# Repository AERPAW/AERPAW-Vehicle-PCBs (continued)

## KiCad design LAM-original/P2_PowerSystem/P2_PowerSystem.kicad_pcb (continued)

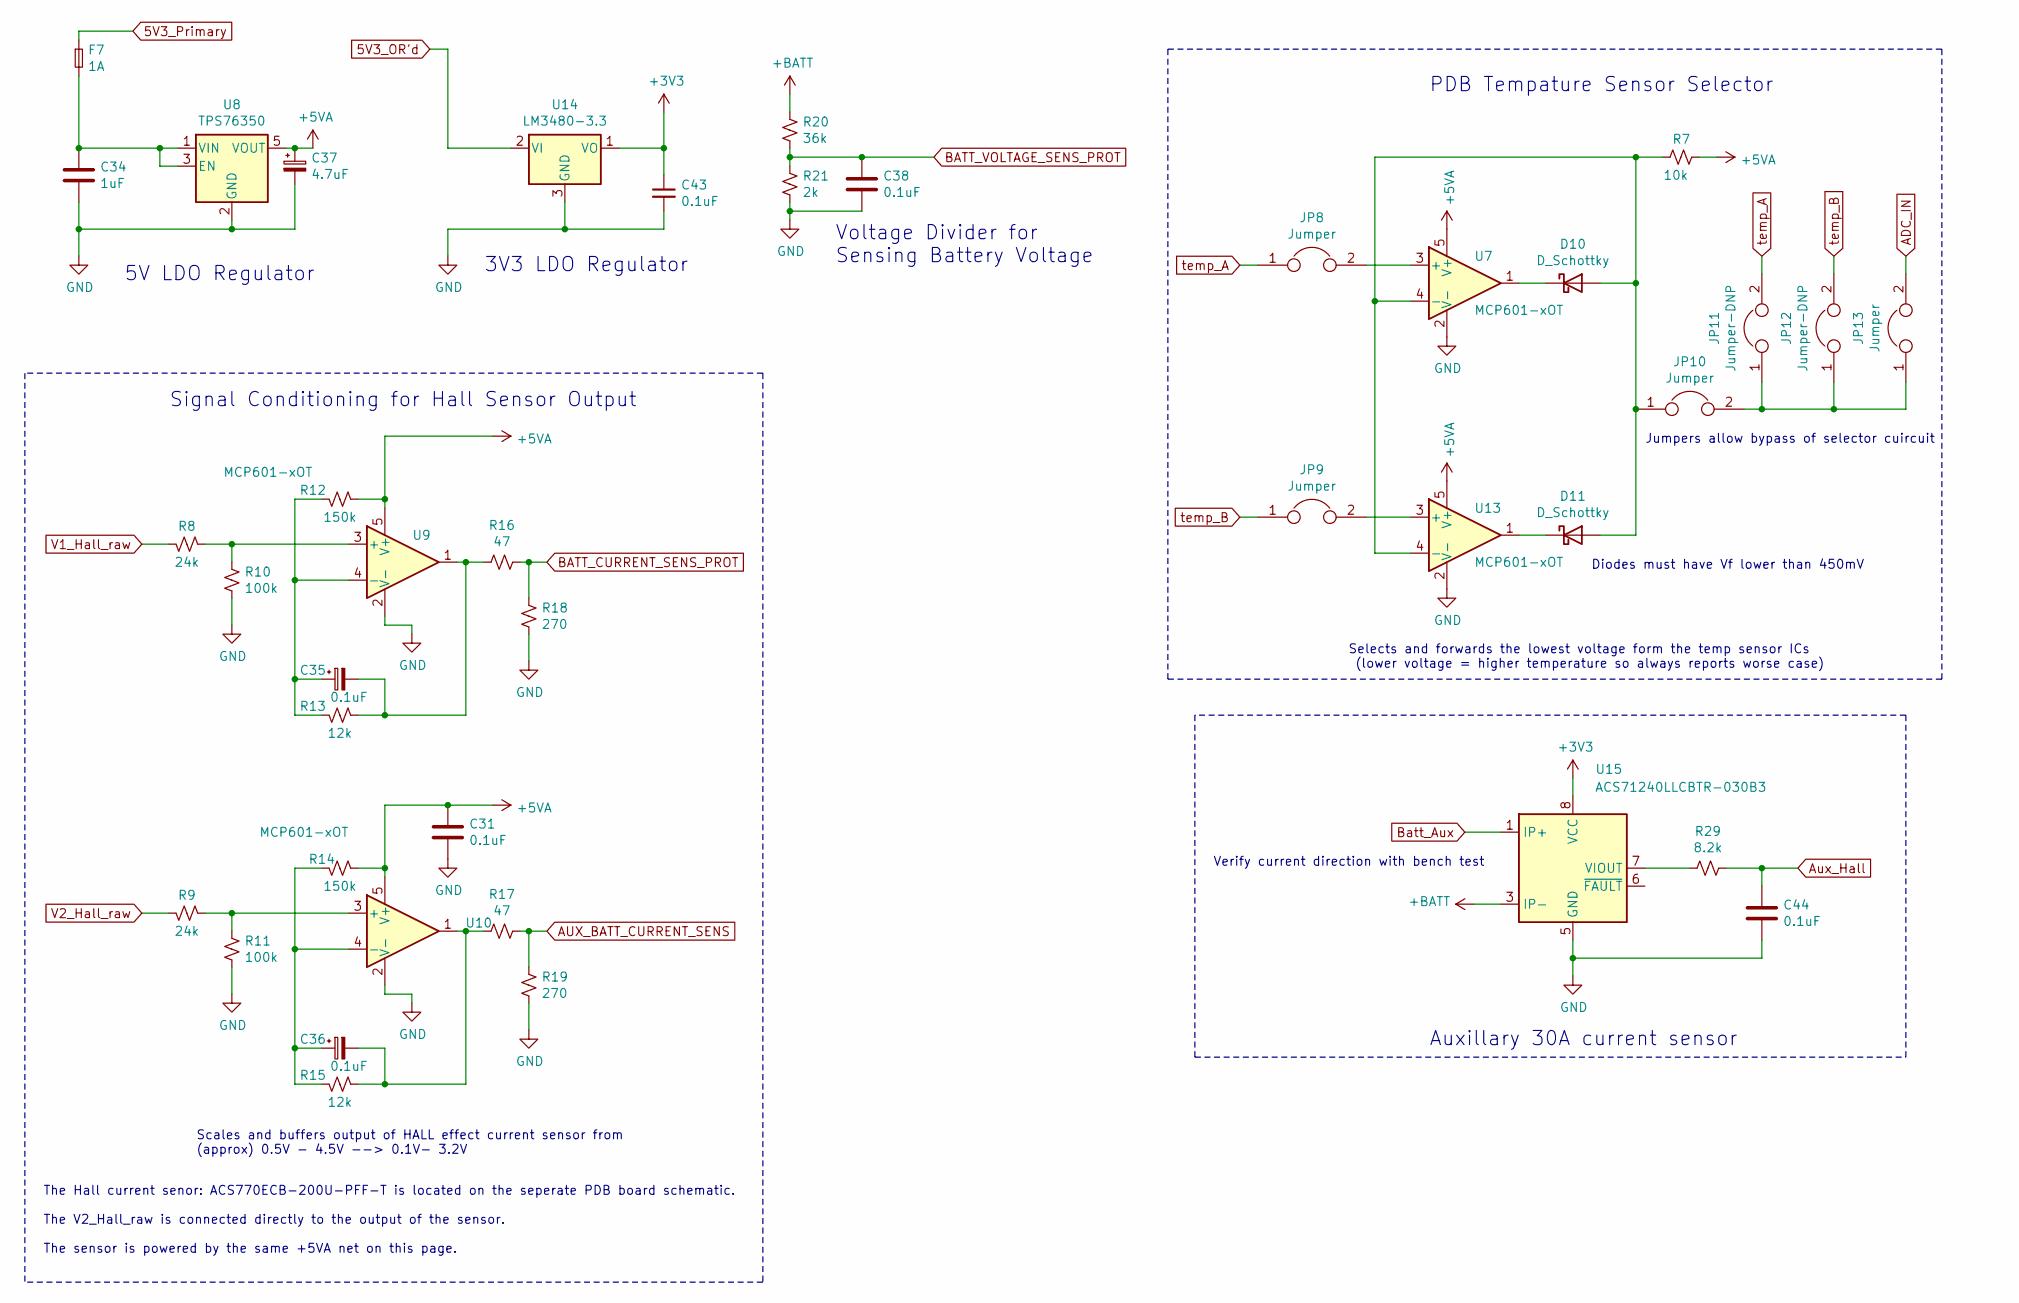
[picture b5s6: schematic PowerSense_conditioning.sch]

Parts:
C31, C35, C36, C38, C43, C44: 0.1uF; C_1206_3216Metric; Meta_Part CAP CER 0.1UF 50V 1206
C34: 1uF; C_1206_3216Metric; Meta_Part CAP CER 1UF 50V 1206
C37: 4.7uF; C_1206_3216Metric; Meta_Part CAP TANT 4.7UF 50V 1206
D10, D11: D_Schottky; D_0603_1608Metric_Castellated; Meta_Part Diode Schottky 0603 Vf < 450mV
F7: 1A; Fuse_1206_3216Metric_Pad1.42x1.75mm_HandSolder; Meta_Part FUSE SMD 1A 60VDC 1206
JP8, JP9, JP10, JP13: Jumper; SolderJumper-2_P1.3mm_Open_RoundedPad1.0x1.5mm; Meta_Part DNP
JP11, JP12: Jumper-DNP; SolderJumper-2_P1.3mm_Open_RoundedPad1.0x1.5mm; Meta_Part DNP
R7: 10k; R_1206_3216Metric; Meta_Part RES 10k OHM 1% 1/4W 1206
R8, R9: 24k; R_1206_3216Metric; Meta_Part RES 24k OHM 1% 1/4W 1206
R10, R11: 100k; R_1206_3216Metric; Meta_Part RES 100k OHM 1% 1/4W 1206
R12, R14: 150k; R_1206_3216Metric; Meta_Part RES 150k OHM 1% 1/4W 1206
R13, R15: 12k; R_1206_3216Metric; Meta_Part RES 12k OHM 1% 1/4W 1206
R16, R17: 47; R_1206_3216Metric; Meta_Part RES 47 OHM 1% 1/4W 1206
R18, R19: 270; R_1206_3216Metric; Meta_Part RES 270 OHM 1% 1/4W 1206
R20: 36k; R_1206_3216Metric; Meta_Part RES 36k OHM 1% 1/4W 1206
R21: 2k; R_1206_3216Metric; Meta_Part RES 2k OHM 1% 1/4W 1206
R29: 8.2k; R_1206_3216Metric; Meta_Part RES 8.2K OHM 1% 1/4W 1206
U7, U9, U10, U13: MCP601-xOT; SOT-23-5; Meta_Part MCP601-xOT
U8: TPS76350; SOT-23-5; Meta_Part TPS76350
U14: LM3480-3.3; SOT-23; Meta_Part Lin Reg 3.3V 0.1A 3-Pin SOT-23
U15: ACS71240LLCBTR-030B3; SOIC-8_3.9x4.9mm_P1.27mm; Meta_Part ACS71240LLCBTR-030B3

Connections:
5V3_OR'd: U14.2 (VI); also elsewhere on the board
5V3_Primary: F7.1; also elsewhere on the board
+3V3: C43.1, U14.1 (VO), U15.8 (VCC)
+5VA: C31.1, C37.1, R7.1, R12.2, R14.2, U7.5 (V+), U8.5 (VOUT), U9.5 (V+), U10.5 (V+), U13.5 (V+); also elsewhere on the board
+BATT: R20.1, U15.3 (IP-), U15.4 (IP-); also elsewhere on the board
ADC_IN: JP13.2; also elsewhere on the board
AUX_BATT_CURRENT_SENS: R17.1, R19.2; also elsewhere on the board
Aux_Hall: C44.1, R29.1; also elsewhere on the board
BATT_CURRENT_SENS_PROT: R16.1, R18.2; also elsewhere on the board
BATT_VOLTAGE_SENS_PROT: C38.1, R20.2, R21.1; also elsewhere on the board
Batt_Aux: U15.1 (IP+), U15.2 (IP+); also elsewhere on the board
GND: C31.2, C34.2, C37.2, C38.2, C43.2, C44.2, R10.1, R11.1, R18.1, R19.1, R21.2, U7.2 (V-), U8.2 (GND), U9.2 (V-), U10.2 (V-), U13.2 (V-), U14.3 (GND), U15.5 (GND); also elsewhere on the board
unnamed: C34.1, F7.2, U8.1 (VIN), U8.3 (EN)
unnamed: C35.1, R12.1, R13.1, U9.4 (-)
unnamed: C35.2, R13.2, R16.2, U9.1
unnamed: C36.1, R14.1, R15.1, U10.4 (-)
unnamed: C36.2, R15.2, R17.2, U10.1
unnamed: D10.1 (K), U7.1
unnamed: D10.2 (A), D11.2 (A), JP10.1, R7.2, U7.4 (-), U13.4 (-)
unnamed: D11.1 (K), U13.1
unnamed: JP8.2, U7.3 (+)
unnamed: JP9.2, U13.3 (+)
unnamed: JP10.2, JP11.1, JP12.1, JP13.1
unnamed: R8.2, R10.2, U9.3 (+)
unnamed: R9.2, R11.2, U10.3 (+)
unnamed: R29.2, U15.7 (VIOUT)
V1_Hall_raw: R8.1; also elsewhere on the board
V2_Hall_raw: R9.1; also elsewhere on the board
temp_A: JP8.1, JP11.2; also elsewhere on the board
temp_B: JP9.1, JP12.2; also elsewhere on the board

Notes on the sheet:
Diodes must have Vf lower than 450mV
Selects and forwards the lowest voltage form the temp sensor ICs (lower voltage = higher temperature so always reports worse case)
Verify current direction with bench test
Auxillary 30A current sensor
Signal Conditioning for Hall Sensor Output
5V LDO Regulator
3V3 LDO Regulator
Voltage Divider for Sensing Battery Voltage
PDB Tempature Sensor Selector
Jumpers allow bypass of selector cuircuit
Scales and buffers output of HALL effect current sensor from (approx) 0.5V - 4.5V --> 0.1V- 3.2V
The Hall current senor: ACS770ECB-200U-PFF-T is located on the seperate PDB board schematic. The V2_Hall_raw is connected directly to the output of the sensor. The sensor is powered by the same +5VA net on this page.

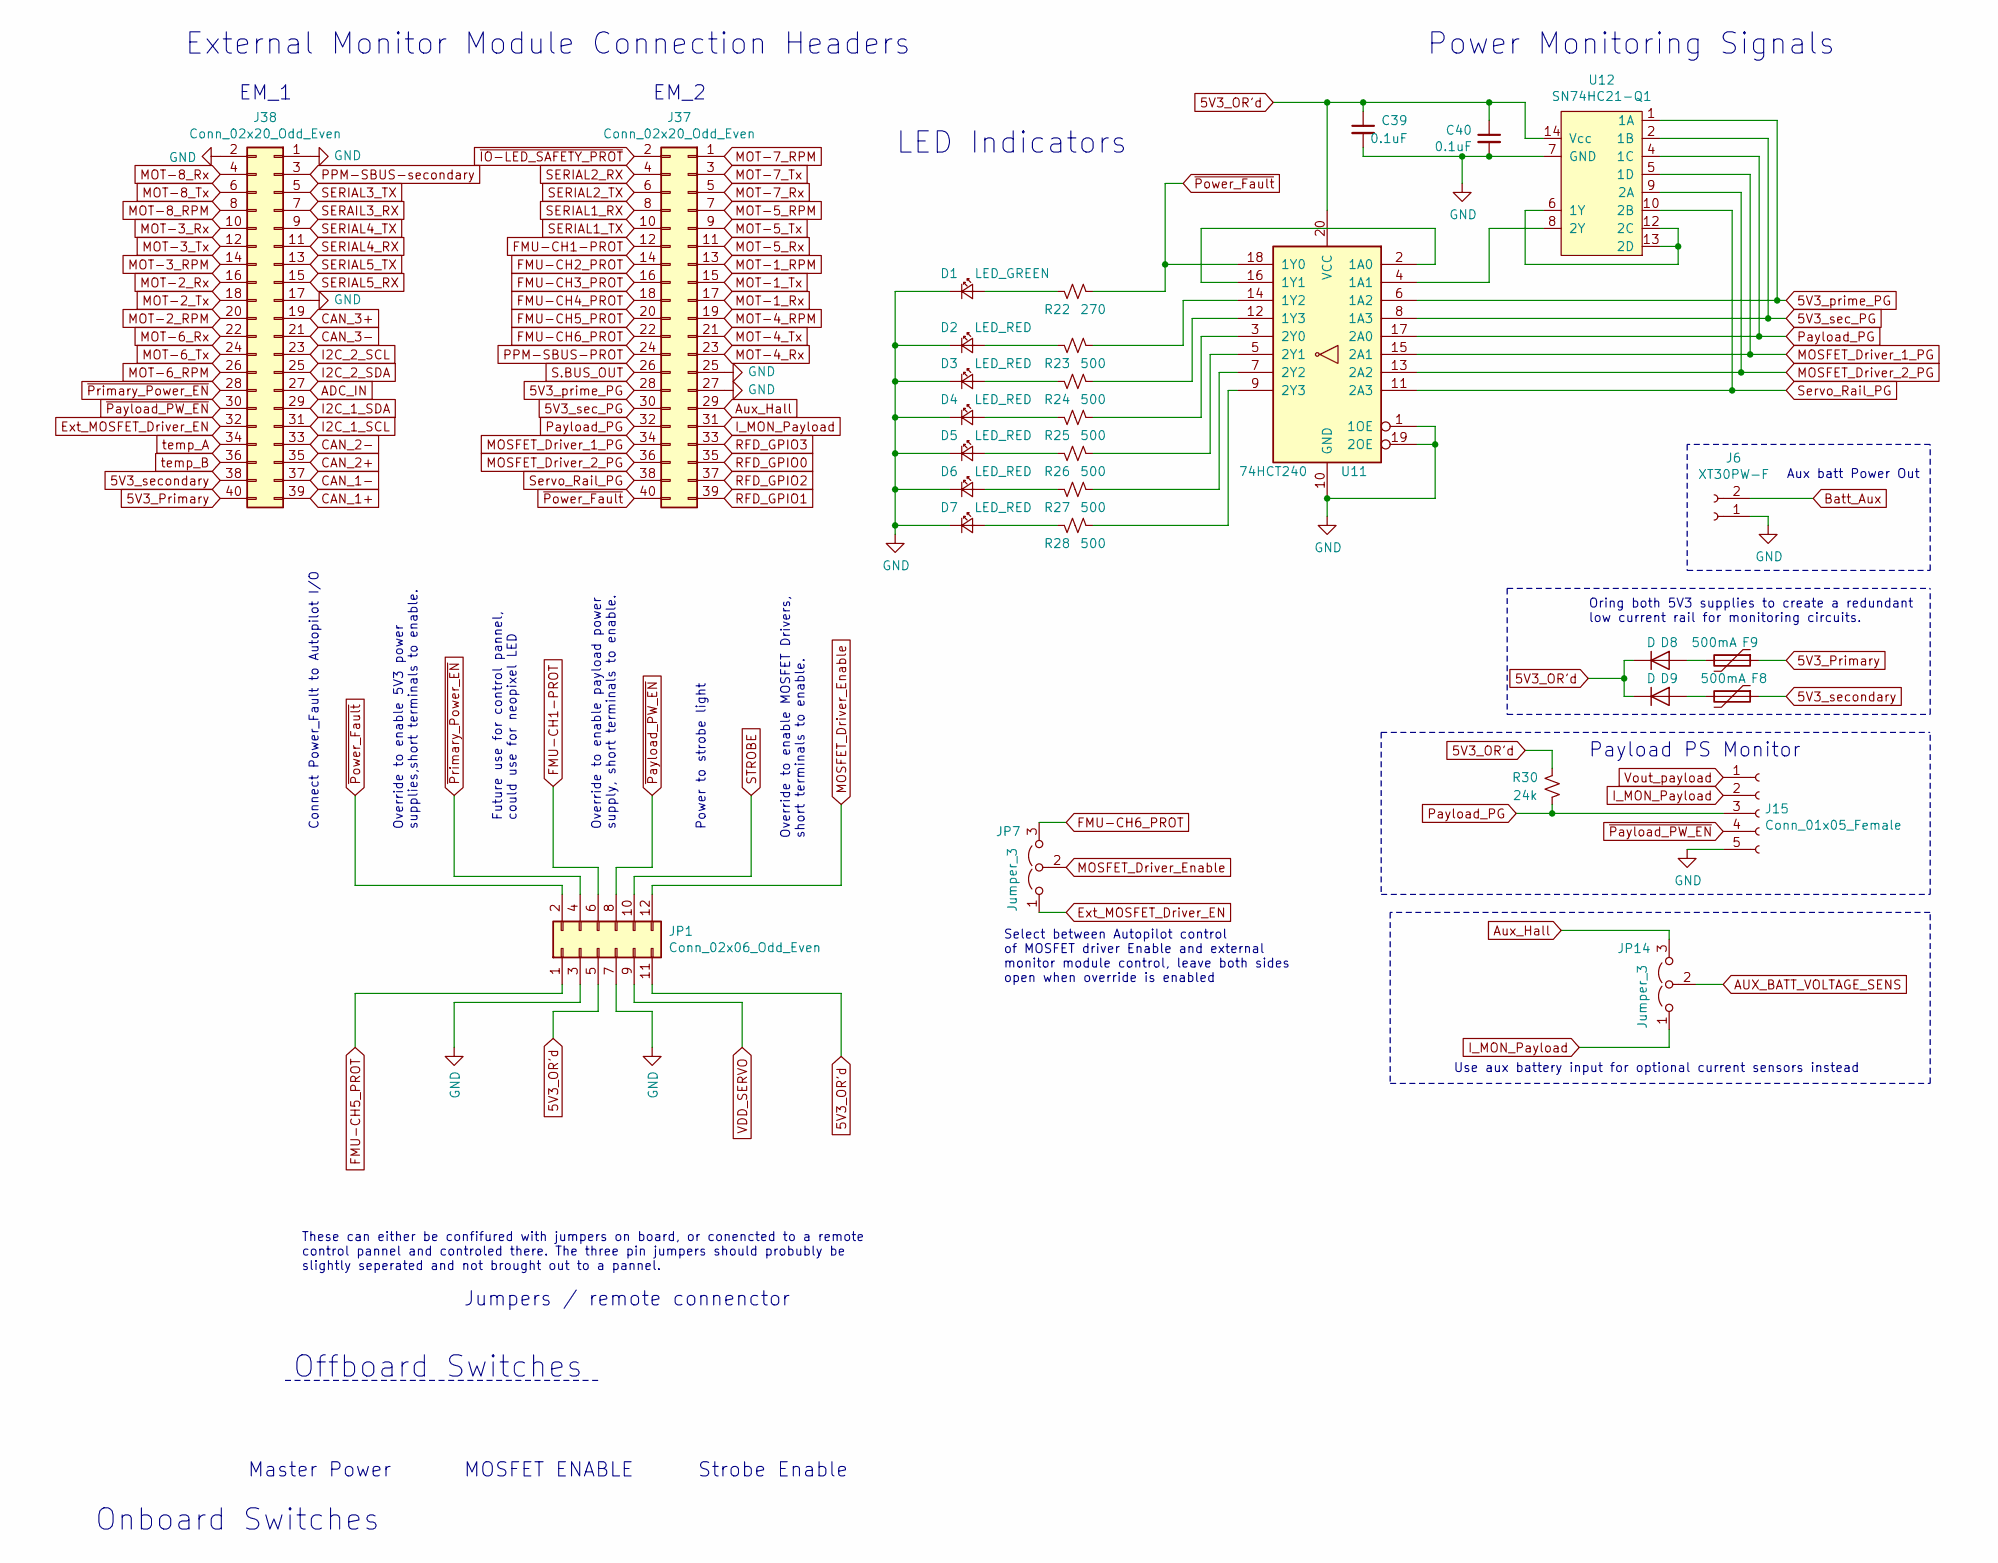
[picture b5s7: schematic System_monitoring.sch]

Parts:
C39, C40: 0.1uF; C_1206_3216Metric; Meta_Part CAP CER 0.1UF 50V 1206
D1: LED_GREEN; LED_1206_3216Metric; Meta_Part LED SMD GREEN 1206
D2, D3, D4, D5, D6, D7: LED_RED; LED_1206_3216Metric; Meta_Part LED SMD RED 1206
D8, D9: D; D_1206_3216Metric; Meta_Part Diode GEN PURP 1206
F8, F9: 500mA; Fuse_1206_3216Metric_Pad1.42x1.75mm_HandSolder; Meta_Part FUSE SMD 0.5A 10VDC 1206
J6: XT30PW-F; AMASS_XT30PW-F_1x02_P2.50mm_Horizontal; Meta_Part XT30PW-F
J15: Conn_01x05_Female; JST_GH_SM05B-GHS-TB_1x05-1MP_P1.25mm_Horizontal; Meta_Part JST-GH 5POS HEADER HORZ
J37, J38: Conn_02x20_Odd_Even; SAMTEC_SFC-120-T2-F-D-A; Meta_Part HEADER-F 0.05\" 2x20 POS SMD
JP1: Conn_02x06_Odd_Even; PinHeader_2x06_P1.27mm_Vertical; Meta_Part HEADER-F 0.05\" 2x6 POS THT
JP7, JP14: Jumper_3; PinHeader_1x03_P1.27mm_Vertical; Meta_Part HEADER-M 0.05\" 3 POS THT
R22: 270; R_1206_3216Metric; Meta_Part RES 270 OHM 1% 1/4W 1206
R23, R24, R25, R26, R27, R28: 500; R_1206_3216Metric; Meta_Part RES 500 OHM 1% 1/4W 1206
R30: 24k; R_1206_3216Metric; Meta_Part RES 24k OHM 1% 1/4W 1206
U11: 74HCT240; TSSOP-20_4.4x6.5mm_P0.65mm; Meta_Part 74HCT240
U12: SN74HC21-Q1; TSSOP-14_4.4x5mm_P0.65mm; Meta_Part SN74HC21-Q1

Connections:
5V3_OR'd: C39.1, C40.1, D8.1 (K), D9.1 (K), JP1.5, JP1.11, R30.2, U11.20 (VCC), U12.14 (Vcc); also elsewhere on the board
5V3_Primary: F9.1, J38.40; also elsewhere on the board
5V3_prime_PG: J37.28, U11.6 (1A2), U12.1 (1A); also elsewhere on the board
5V3_sec_PG: J37.30, U11.8 (1A3), U12.2 (1B); also elsewhere on the board
5V3_secondary: F8.1, J38.38; also elsewhere on the board
ADC_IN: J38.27; also elsewhere on the board
AUX_BATT_VOLTAGE_SENS: JP14.2 (C); also elsewhere on the board
Aux_Hall: J37.29, JP14.3 (B); also elsewhere on the board
Batt_Aux: J6.2; also elsewhere on the board
CAN_1+: J38.39; also elsewhere on the board
CAN_1-: J38.37; also elsewhere on the board
CAN_2+: J38.35; also elsewhere on the board
CAN_2-: J38.33; also elsewhere on the board
CAN_3+: J38.19; also elsewhere on the board
CAN_3-: J38.21; also elsewhere on the board
Ext_MOSFET_Driver_EN: J38.32, JP7.1 (A)
FMU-CH1-PROT: J37.12, JP1.6; also elsewhere on the board
FMU-CH2_PROT: J37.14; also elsewhere on the board
FMU-CH3_PROT: J37.16; also elsewhere on the board
FMU-CH4_PROT: J37.18; also elsewhere on the board
FMU-CH5_PROT: J37.20, JP1.1; also elsewhere on the board
FMU-CH6_PROT: J37.22, JP7.3 (B); also elsewhere on the board
GND: C39.2, C40.2, D1.1 (K), D2.1 (K), D3.1 (K), D4.1 (K), D5.1 (K), D6.1 (K), D7.1 (K), J6.1, J15.5, J37.25, J37.27, J38.1, J38.2, J38.17, JP1.3, JP1.7, U11.1 (1OE), U11.10 (GND), U11.19 (2OE), U12.7 (GND); also elsewhere on the board
I2C_1_SCL: J38.31; also elsewhere on the board
I2C_1_SDA: J38.29; also elsewhere on the board
I2C_2_SCL: J38.23; also elsewhere on the board
I2C_2_SDA: J38.25; also elsewhere on the board
I_MON_Payload: J15.2, J37.31, JP14.1 (A)
MOSFET_Driver_1_PG: J37.34, U11.15 (2A1), U12.5 (1D); also elsewhere on the board
MOSFET_Driver_2_PG: J37.36, U11.13 (2A2), U12.9 (2A); also elsewhere on the board
MOSFET_Driver_Enable: JP1.12, JP7.2 (C); also elsewhere on the board
MOT-1_RPM: J37.13; also elsewhere on the board
MOT-1_Rx: J37.17; also elsewhere on the board
MOT-1_Tx: J37.15; also elsewhere on the board
MOT-2_RPM: J38.20; also elsewhere on the board
MOT-2_Rx: J38.16; also elsewhere on the board
MOT-2_Tx: J38.18; also elsewhere on the board
MOT-3_RPM: J38.14; also elsewhere on the board
MOT-3_Rx: J38.10; also elsewhere on the board
MOT-3_Tx: J38.12; also elsewhere on the board
MOT-4_RPM: J37.19; also elsewhere on the board
MOT-4_Rx: J37.23; also elsewhere on the board
MOT-4_Tx: J37.21; also elsewhere on the board
MOT-5_RPM: J37.7; also elsewhere on the board
MOT-5_Rx: J37.11; also elsewhere on the board
MOT-5_Tx: J37.9; also elsewhere on the board
MOT-6_RPM: J38.26; also elsewhere on the board
MOT-6_Rx: J38.22; also elsewhere on the board
MOT-6_Tx: J38.24; also elsewhere on the board
MOT-7_RPM: J37.1; also elsewhere on the board
MOT-7_Rx: J37.5; also elsewhere on the board
MOT-7_Tx: J37.3; also elsewhere on the board
MOT-8_RPM: J38.8; also elsewhere on the board
MOT-8_Rx: J38.4; also elsewhere on the board
MOT-8_Tx: J38.6; also elsewhere on the board
unnamed: D1.2 (A), R22.2
unnamed: D2.2 (A), R23.2
unnamed: D3.2 (A), R24.2
unnamed: D4.2 (A), R25.2
unnamed: D5.2 (A), R26.2
unnamed: D6.2 (A), R27.2
unnamed: D7.2 (A), R28.2
unnamed: D8.2 (A), F9.2
unnamed: D9.2 (A), F8.2
unnamed: R23.1, U11.14 (1Y2)
unnamed: R24.1, U11.12 (1Y3)
unnamed: R25.1, U11.3 (2Y0)
unnamed: R26.1, U11.5 (2Y1)
unnamed: R27.1, U11.7 (2Y2)
unnamed: R28.1, U11.9 (2Y3)
unnamed: U11.4 (1A1), U12.8 (2Y)
unnamed: U11.2 (1A0), U11.16 (1Y1)
unnamed: U12.6 (1Y), U12.12 (2C), U12.13 (2D)
PPM-SBUS-PROT: J37.24; also elsewhere on the board
PPM-SBUS-secondary: J38.3; also elsewhere on the board
Payload_PG: J15.3, J37.32, R30.1, U11.17 (2A0), U12.4 (1C); also elsewhere on the board
RFD_GPIO0: J37.35; also elsewhere on the board
RFD_GPIO1: J37.39; also elsewhere on the board
RFD_GPIO2: J37.37; also elsewhere on the board
RFD_GPIO3: J37.33; also elsewhere on the board
S.BUS_OUT: J37.26; also elsewhere on the board
SERAIL3_RX: J38.7; also elsewhere on the board
SERIAL1_RX: J37.8; also elsewhere on the board
SERIAL1_TX: J37.10; also elsewhere on the board
SERIAL2_RX: J37.4; also elsewhere on the board
SERIAL2_TX: J37.6; also elsewhere on the board
SERIAL3_TX: J38.5; also elsewhere on the board
SERIAL4_RX: J38.11; also elsewhere on the board
SERIAL4_TX: J38.9; also elsewhere on the board
SERIAL5_RX: J38.15; also elsewhere on the board
SERIAL5_TX: J38.13; also elsewhere on the board
STROBE: JP1.10; also elsewhere on the board
Servo_Rail_PG: J37.38, U11.11 (2A3), U12.10 (2B); also elsewhere on the board
VDD_SERVO: JP1.9; also elsewhere on the board
Vout_payload: J15.1
temp_A: J38.34; also elsewhere on the board
temp_B: J38.36; also elsewhere on the board
~IO-LED_SAFETY_PROT: J37.2; also elsewhere on the board
~Payload_PW_EN: J15.4, J38.30, JP1.8
~Power_Fault: J37.40, JP1.2, R22.1, U11.18 (1Y0)
~Primary_Power_EN: J38.28, JP1.4; also elsewhere on the board

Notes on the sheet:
External Monitor Module Connection Headers
LED Indicators
Offboard Switches
Override to enable payload power supply, short terminals to enable.
Override to enable 5V3 power supplies,short terminals to enable.
Override to enable MOSFET Drivers, short terminals to enable.
Select between Autopilot control of MOSFET driver Enable and external monitor module control, leave both sides open when override is enabled
Power Monitoring Signals
Onboard Switches
Connect Power_Fault to Autopilot I/O
Oring both 5V3 supplies to create a redundant low current rail for monitoring circuits.
Master Power
MOSFET ENABLE
Strobe Enable
Payload PS Monitor
Aux batt Power Out
Power to strobe light
Future use for control pannel, could use for neopixel LED
These can either be confifured with jumpers on board, or conencted to a remote control pannel and controled there. The three pin jumpers should probubly be slightly seperated and not brought out to a pannel.
Jumpers / remote connenctor
EM_1
EM_2
Use aux battery input for optional current sensors instead

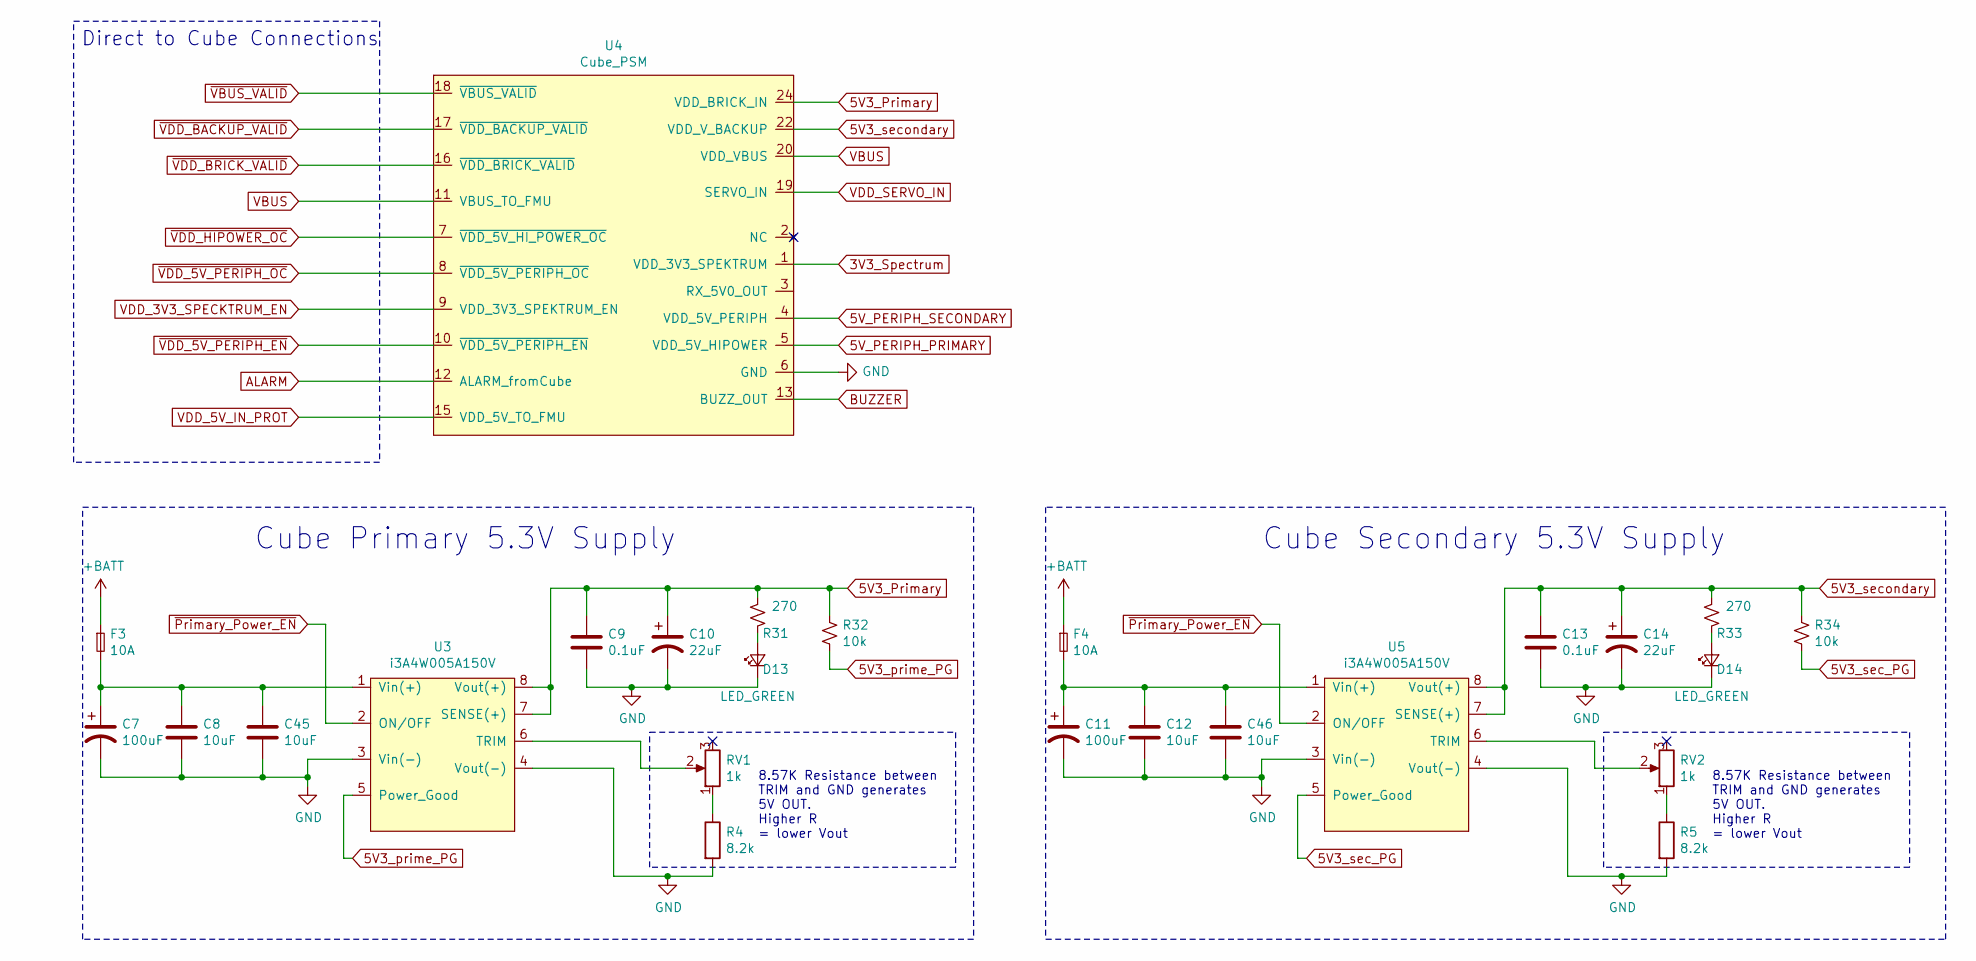
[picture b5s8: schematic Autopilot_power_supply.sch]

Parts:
C7, C11: 100uF; CP_Elec_10x10.5; Meta_Part CAP ALUM 100UF 20% 63V SMD
C8, C12, C45, C46: 10uF; C_1206_3216Metric; Meta_Part CAP CER 10UF 50V 1206
C9, C13: 0.1uF; C_1206_3216Metric; Meta_Part CAP CER 0.1UF 50V 1206
C10, C14: 22uF; C_1206_3216Metric; Meta_Part CAP CER 22UF 35V 1206
D13, D14: LED_GREEN; LED_1206_3216Metric; Meta_Part LED SMD GREEN 1206
F3, F4: 10A; Fuse_2512_6332Metric_Pad1.52x3.35mm_HandSolder; Meta_Part FUSE SMD 10A 60VDC 2-SMD
R4, R5: 8.2k; R_1206_3216Metric; Meta_Part RES 8.2K OHM 1% 1/4W 1206
R31, R33: 270; R_1206_3216Metric; Meta_Part RES 270 OHM 1% 1/4W 1206
R32, R34: 10k; R_1206_3216Metric; Meta_Part RES 10k OHM 1% 1/4W 1206
RV1, RV2: 1k; Potentiometer_Bourns_3266W_Vertical; Meta_Part 12 TURN TRIMMER 1K OHM 0.25W PC PIN TOP
U3, U5: i3A4W005A150V; 1_32nd_Brick_8pin; Meta_Part i3A4W005A150V
U4: Cube_PSM; PSM; Meta_Part Cube PSM

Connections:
3V3_Spectrum: U4.1 (VDD_3V3_SPEKTRUM)
5V3_Primary: C9.1, C10.1, R31.1, R32.2, U3.7 (SENSE(+)), U3.8 (Vout(+)), U4.24 (VDD_BRICK_IN); also elsewhere on the board
5V3_prime_PG: R32.1, U3.5 (Power_Good); also elsewhere on the board
5V3_sec_PG: R34.1, U5.5 (Power_Good); also elsewhere on the board
5V3_secondary: C13.1, C14.1, R33.1, R34.2, U4.22 (VDD_V_BACKUP), U5.7 (SENSE(+)), U5.8 (Vout(+)); also elsewhere on the board
5V_PERIPH_PRIMARY: U4.5 (VDD_5V_HIPOWER); also elsewhere on the board
5V_PERIPH_SECONDARY: U4.4 (VDD_5V_PERIPH); also elsewhere on the board
+BATT: F3.1, F4.1; also elsewhere on the board
ALARM: U4.12 (ALARM_fromCube); also elsewhere on the board
BUZZER: U4.13 (BUZZ_OUT); also elsewhere on the board
GND: C7.2, C8.2, C9.2, C10.2, C11.2, C12.2, C13.2, C14.2, C45.2, C46.2, D13.1 (K), D14.1 (K), R4.2, R5.2, U3.3 (Vin(-)), U3.4 (Vout(-)), U4.6 (GND), U5.3 (Vin(-)), U5.4 (Vout(-)); also elsewhere on the board
unnamed: C11.1, C12.1, C46.1, F4.2, U5.1 (Vin(+))
unnamed: C7.1, C8.1, C45.1, F3.2, U3.1 (Vin(+))
unnamed: D13.2 (A), R31.2
unnamed: D14.2 (A), R33.2
unnamed: R4.1, RV1.1
unnamed: R5.1, RV2.1
unnamed: RV1.2, U3.6 (TRIM)
unnamed: RV2.2, U5.6 (TRIM)
VBUS: U4.11 (VBUS_TO_FMU), U4.20 (VDD_VBUS); also elsewhere on the board
VDD_3V3_SPECKTRUM_EN: U4.9 (VDD_3V3_SPEKTRUM_EN); also elsewhere on the board
VDD_5V_IN_PROT: U4.15 (VDD_5V_TO_FMU); also elsewhere on the board
VDD_SERVO_IN: U4.19 (SERVO_IN); also elsewhere on the board
~Primary_Power_EN: U3.2 (ON/OFF), U5.2 (ON/OFF); also elsewhere on the board
~VBUS_VALID: U4.18 (~VBUS_VALID); also elsewhere on the board
~VDD_5V_PERIPH_EN: U4.10 (~VDD_5V_PERIPH_EN); also elsewhere on the board
~VDD_5V_PERIPH_OC: U4.8 (~VDD_5V_PERIPH_OC); also elsewhere on the board
~VDD_BACKUP_VALID: U4.17 (~VDD_BACKUP_VALID); also elsewhere on the board
~VDD_BRICK_VALID: U4.16 (~VDD_BRICK_VALID); also elsewhere on the board
~VDD_HIPOWER_OC: U4.7 (~VDD_5V_HI_POWER_OC); also elsewhere on the board

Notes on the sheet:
Direct to Cube Connections
8.57K Resistance between TRIM and GND generates 5V OUT. Higher R = lower Vout
Cube Primary 5.3V Supply
Cube Secondary 5.3V Supply

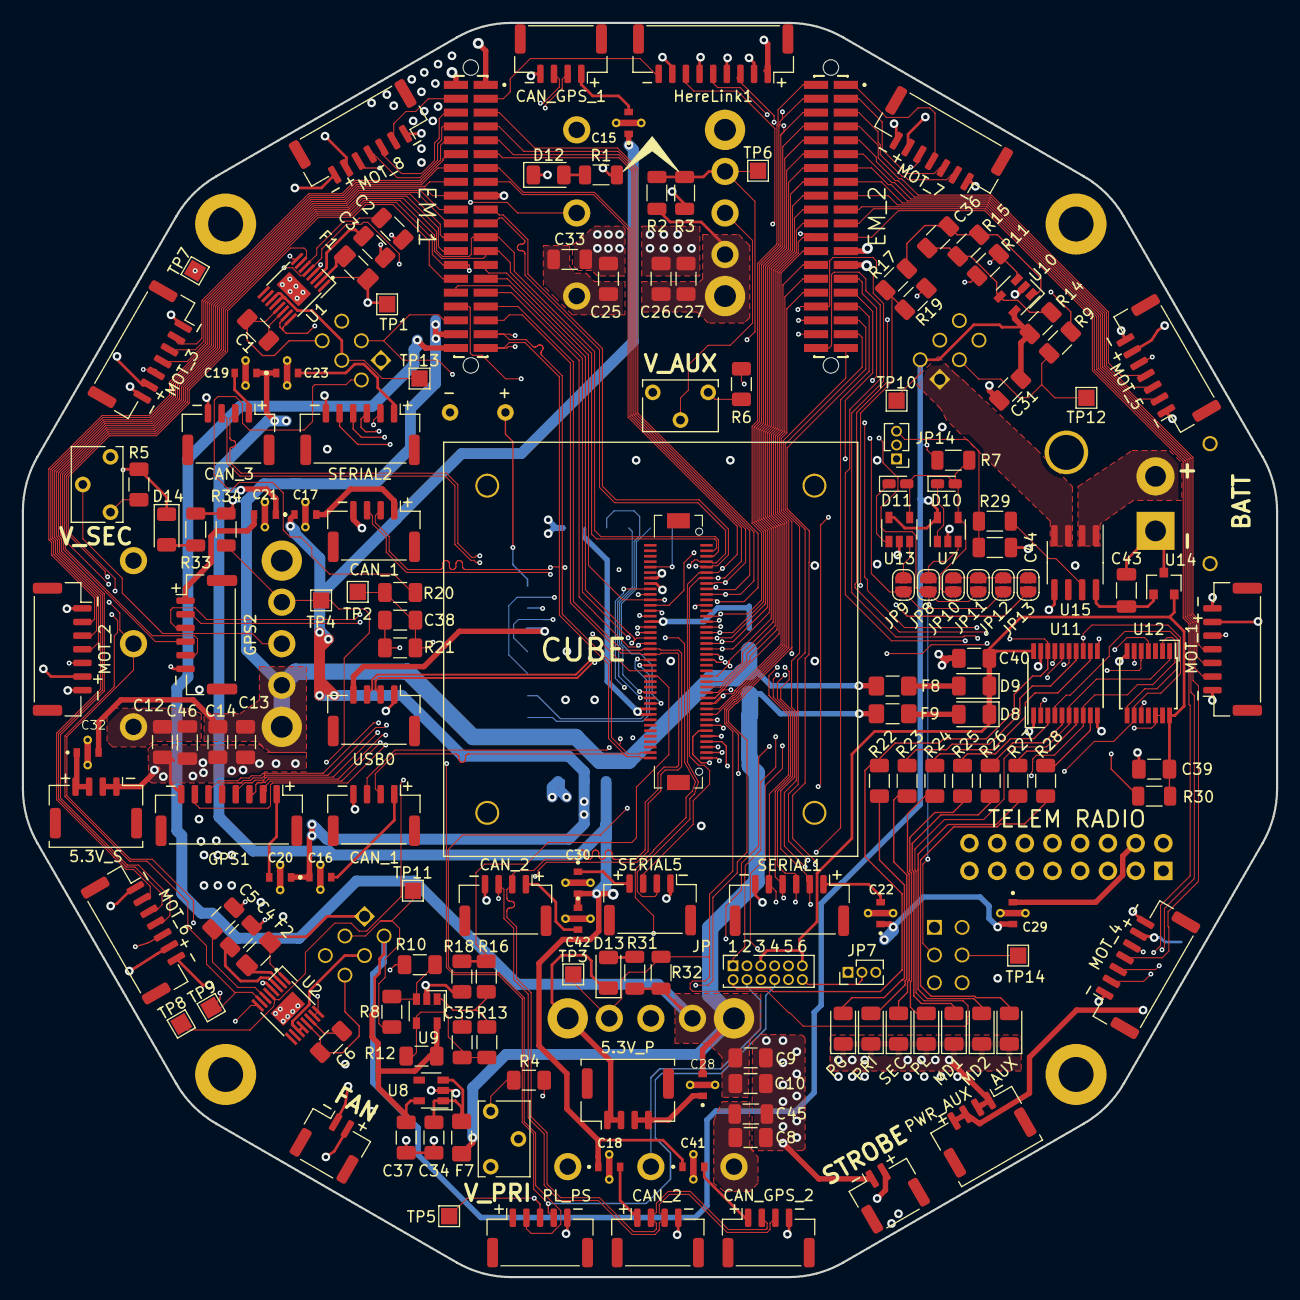
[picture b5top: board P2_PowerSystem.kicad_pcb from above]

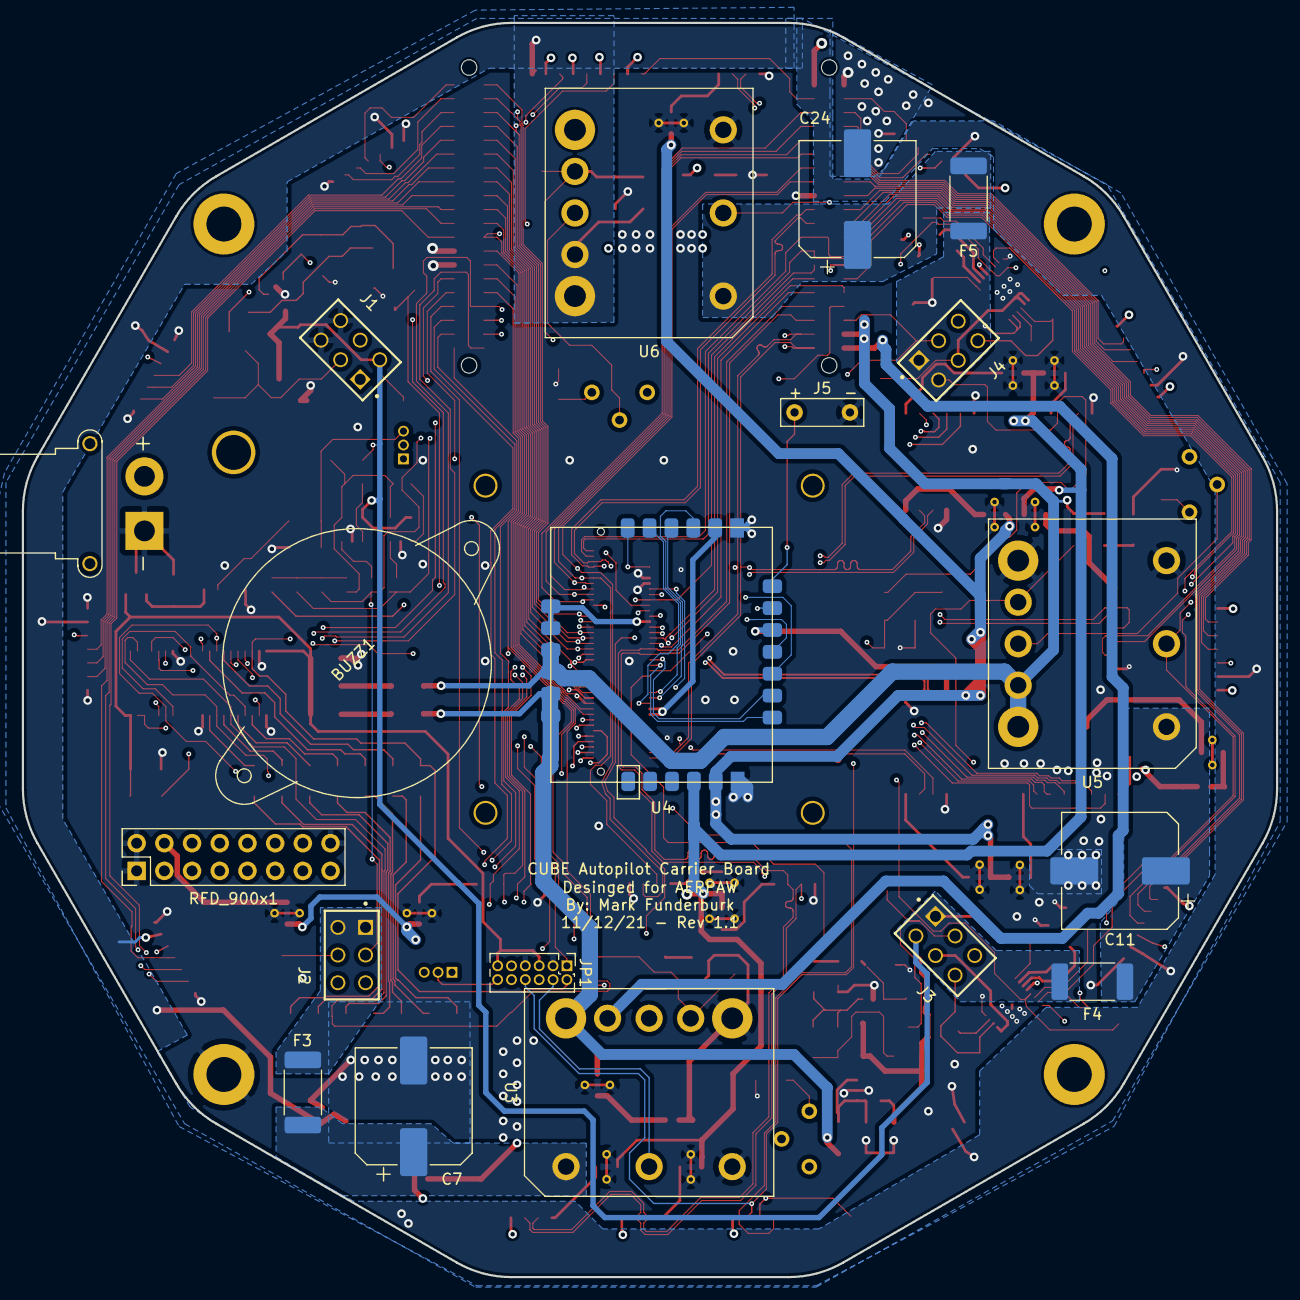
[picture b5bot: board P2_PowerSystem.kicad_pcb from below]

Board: 4 copper layers, 115.0 x 115.0 mm, 186 parts (19 on the bottom side), 189 nets.

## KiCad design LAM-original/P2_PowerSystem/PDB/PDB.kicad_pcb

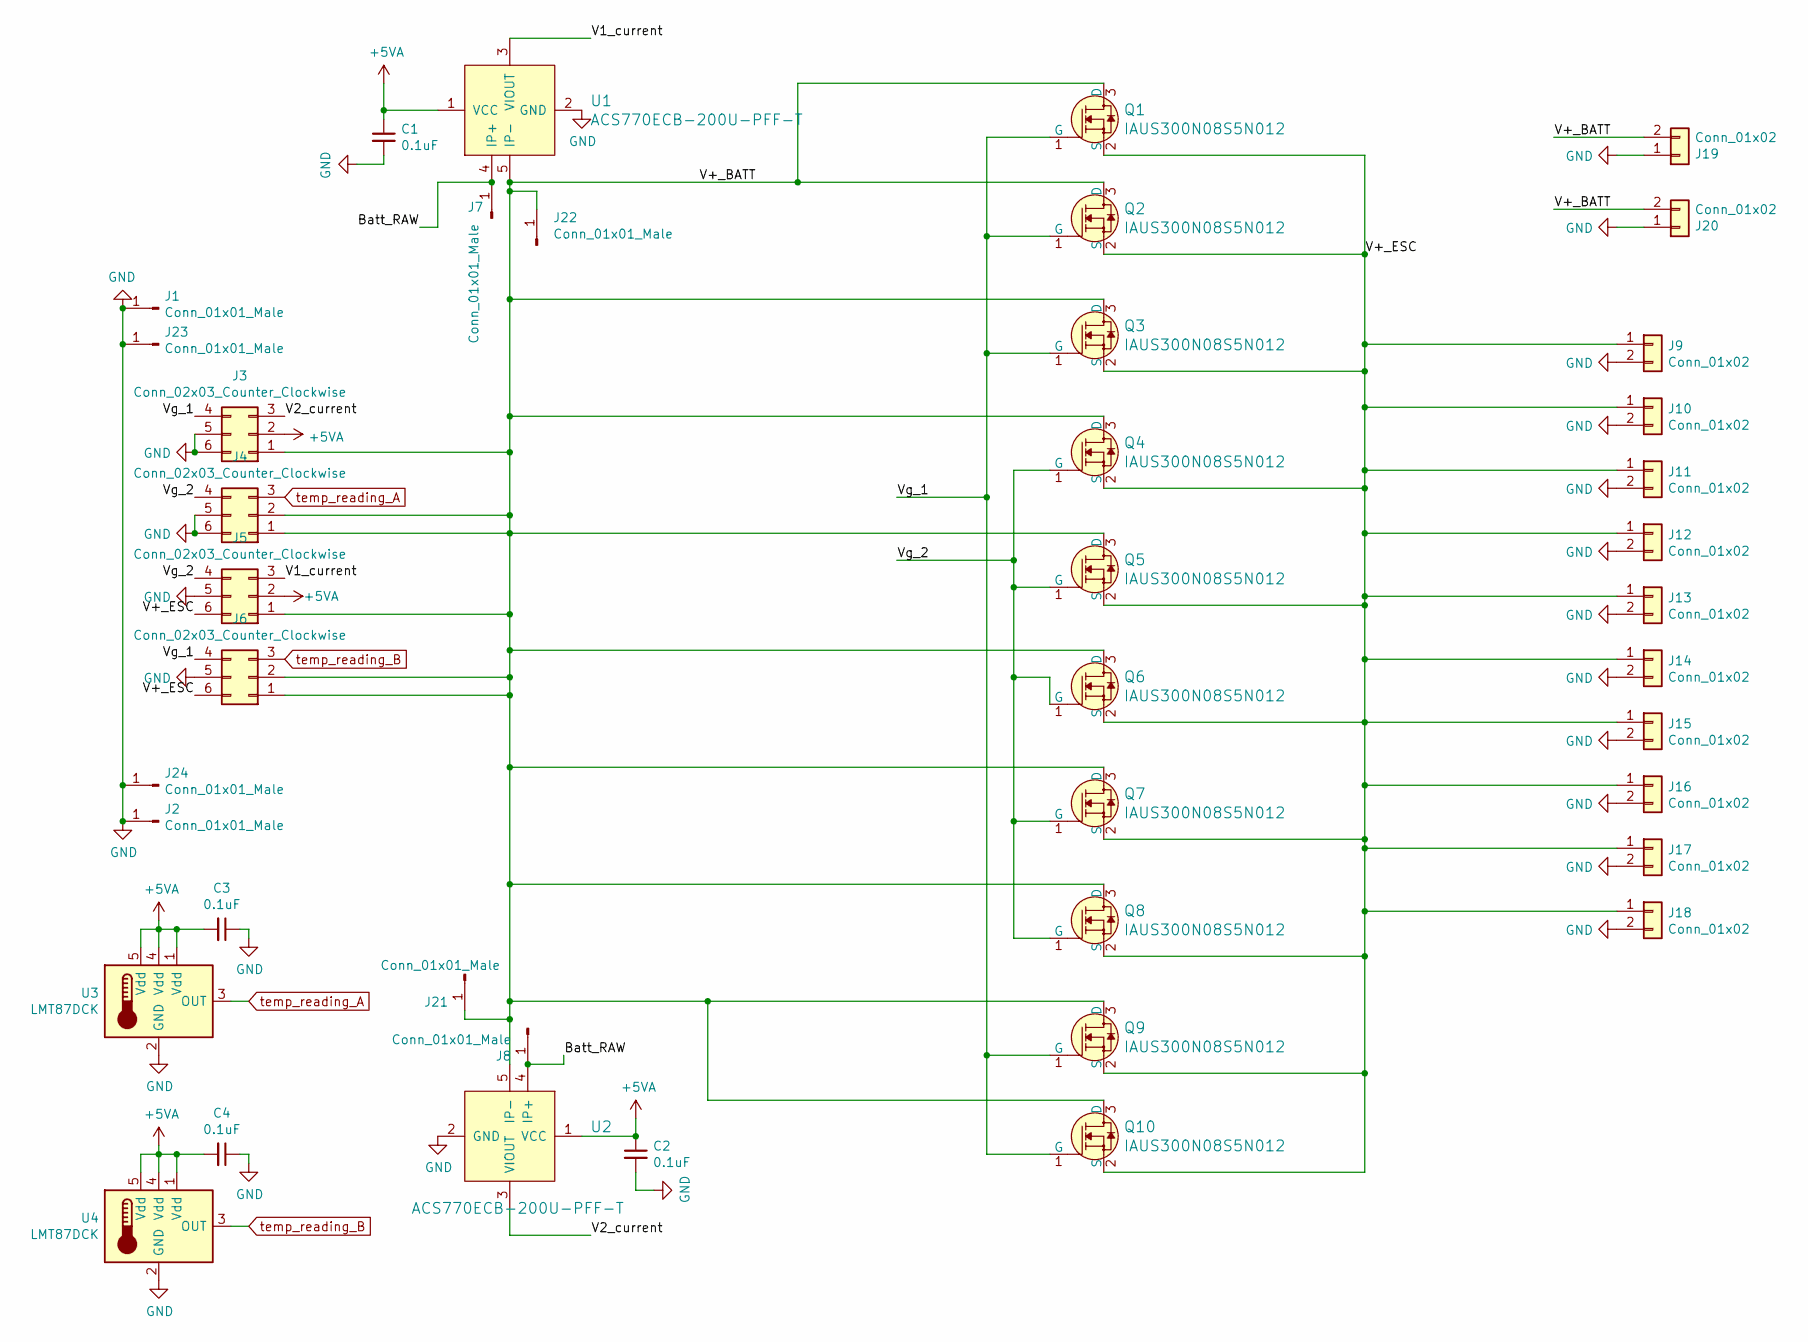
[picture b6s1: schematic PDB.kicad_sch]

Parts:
C1, C2: 0.1uF; C_1206_3216Metric_Pad1.42x1.75mm_HandSolder
C3, C4: 0.1uF; C_0603_1608Metric
J1, J2, J7, J8: Conn_01x01_Male; Pin_D1.3mm_L11.3mm_W2.8mm_Flat
J3, J4, J5, J6: Conn_02x03_Counter_Clockwise; PinHeader_2x03_P2.54mm_Vertical
J9, J10, J11, J12, J13, J14, J15, J16, J17, J18: Conn_01x02; XT-60_horizontal
J19, J20: Conn_01x02; AMASS_XT30PW-F_1x02_P2.50mm_Horizontal
J21, J22: Conn_01x01_Male; Wire_Pad_8x8mm
J23, J24: Conn_01x01_Male; MountingHole_4mm_Pad
Q1, Q2, Q3, Q4, Q5, Q6, Q7, Q8, Q9, Q10: IAUS300N08S5N012; Infineon_PG-HSOF-8-1; MPN IAUS300N08S5N012ATMA1
U1, U2: ACS770ECB-200U-PFF-T; CB-5_Formed_Leads; MPN ACS770ECB-200U-PFF-T
U3, U4: LMT87DCK; SOT-353_SC-70-5

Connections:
+5VA: C1.1, C2.1, C3.2, C4.2, J3.2, J5.2, U1.1 (VCC), U2.1 (VCC), U3.1 (Vdd), U3.4 (Vdd), U3.5 (Vdd), U4.1 (Vdd), U4.4 (Vdd), U4.5 (Vdd)
/Batt_RAW: J7.1, J8.1, U1.4 (IP+), U2.4 (IP+)
/V1_current: J5.3, U1.3 (VIOUT)
/V2_current: J3.3, U2.3 (VIOUT)
/V+_BATT: J3.1, J4.1, J4.2, J5.1, J6.1, J6.2, J19.2, J20.2, J21.1, J22.1, Q1.3 (D), Q2.3 (D), Q3.3 (D), Q4.3 (D), Q5.3 (D), Q6.3 (D), Q7.3 (D), Q8.3 (D), Q9.3 (D), Q10.3 (D), U1.5 (IP-), U2.5 (IP-)
/V+_ESC: J5.6, J6.6, J9.1, J10.1, J11.1, J12.1, J13.1, J14.1, J15.1, J16.1, J17.1, J18.1, Q1.2 (S), Q2.2 (S), Q3.2 (S), Q4.2 (S), Q5.2 (S), Q6.2 (S), Q7.2 (S), Q8.2 (S), Q9.2 (S), Q10.2 (S)
/Vg_1: J3.4, J6.4, Q1.1 (G), Q2.1 (G), Q3.1 (G), Q9.1 (G), Q10.1 (G)
/Vg_2: J4.4, J5.4, Q4.1 (G), Q5.1 (G), Q6.1 (G), Q7.1 (G), Q8.1 (G)
GND: C1.2, C2.2, C3.1, C4.1, J1.1, J2.1, J3.5, J3.6, J4.5, J4.6, J5.5, J6.5, J9.2, J10.2, J11.2, J12.2, J13.2, J14.2, J15.2, J16.2, J17.2, J18.2, J19.1, J20.1, J23.1, J24.1, U1.2 (GND), U2.2 (GND), U3.2 (GND), U4.2 (GND); also elsewhere on the board
temp_reading_A: J4.3, U3.3 (OUT)
temp_reading_B: J6.3, U4.3 (OUT)
